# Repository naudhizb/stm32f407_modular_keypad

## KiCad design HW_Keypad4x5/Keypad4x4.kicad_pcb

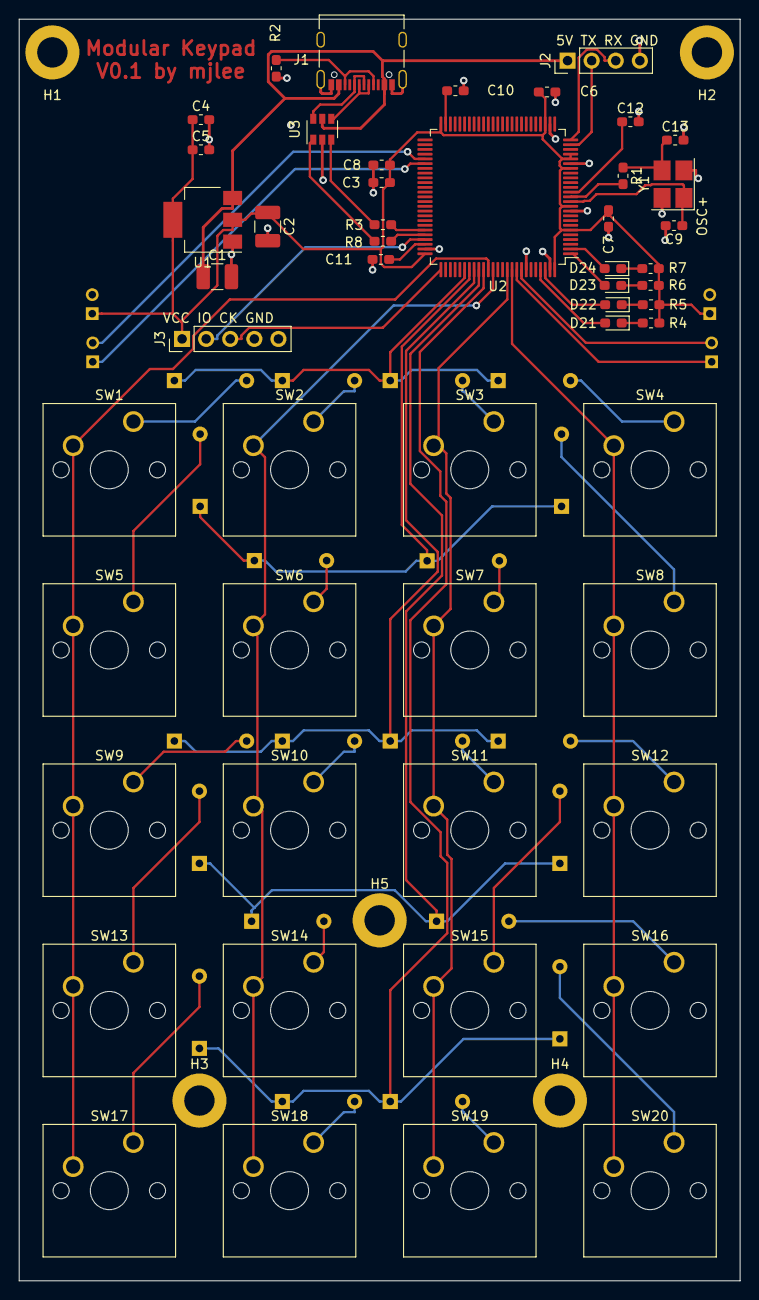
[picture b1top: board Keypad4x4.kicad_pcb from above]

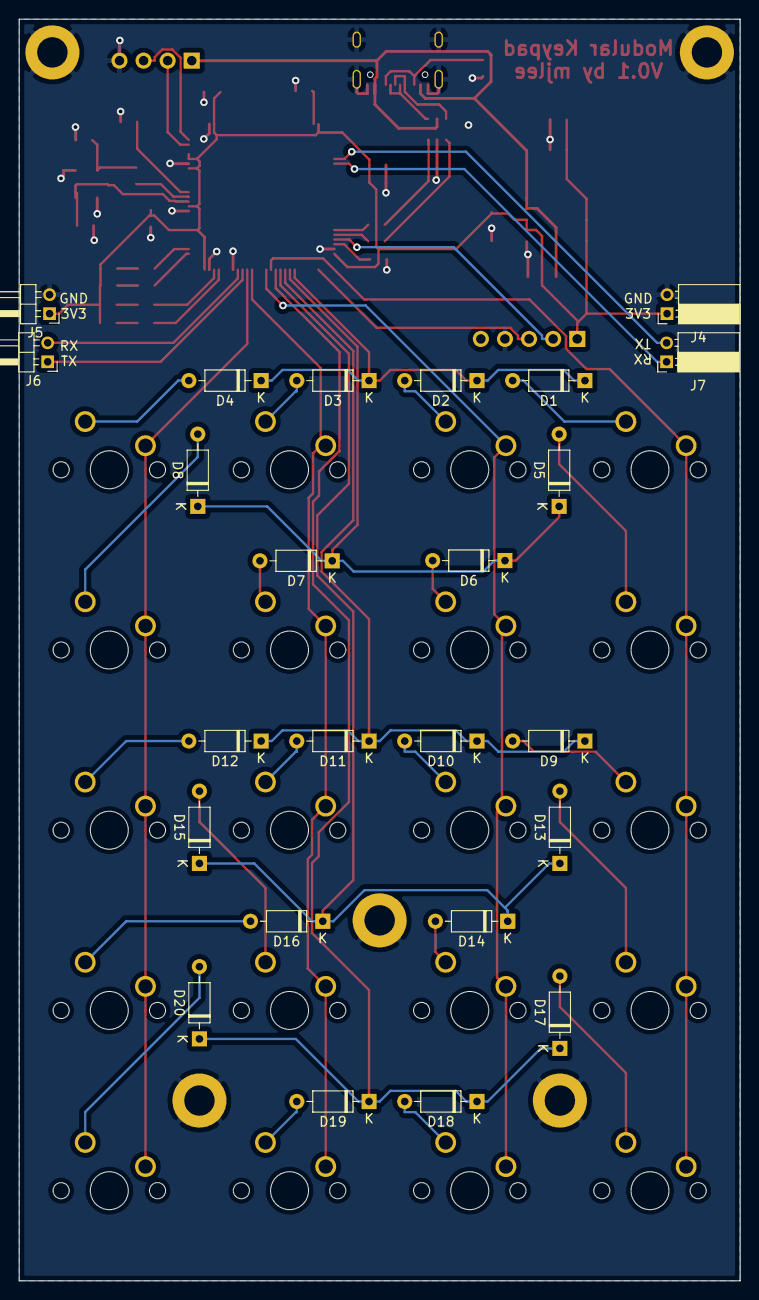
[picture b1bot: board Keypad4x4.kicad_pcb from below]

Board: 2 copper layers, 76.0 x 133.0 mm, 81 parts (24 on the bottom side), 61 nets.

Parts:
C1, C2: 10uF; C_1210_3225Metric_Pad1.42x2.65mm_HandSolder
C3: C475; C_0603_1608Metric_Pad1.05x0.95mm_HandSolder
C4, C5, C6, C7, C8, C12: C104; C_0603_1608Metric_Pad1.05x0.95mm_HandSolder
C9, C13: 12pF; C_0603_1608Metric_Pad1.05x0.95mm_HandSolder
C10, C11: C225; C_0603_1608Metric_Pad1.05x0.95mm_HandSolder
D1, D2, D3, D4, D5, D6, D7, D8, D9, D10, D11, D12, D13, D14, D15, D16, D17, D18, D19, D20: 1N4148; D_DO-35_SOD27_P7.62mm_Horizontal
D21, D22, D23, D24: LED; D_0603_1608Metric_Pad1.05x0.95mm_HandSolder
H1, H2, H3, H4, H5: MountingHole_3.2mm_M3_ISO7380_Pad
J1: USB_C_Receptacle_USB2.0; USB_C_Receptacle_Palconn_UTC16-G
J2: Conn_01x04; PinHeader_1x04_P2.54mm_Vertical
J3: Conn_01x05; PinHeader_1x05_P2.54mm_Vertical
J4: L_Power; PinSocket_1x02_P2.00mm_Horizontal
J5: R_Power; PinHeader_1x02_P2.00mm_Horizontal
J6: R_Comm; PinHeader_1x02_P2.00mm_Horizontal
J7: L_Comm; PinSocket_1x02_P2.00mm_Horizontal
R1: R470; C_0603_1608Metric_Pad1.05x0.95mm_HandSolder
R2: R513; C_0603_1608Metric_Pad1.05x0.95mm_HandSolder
R3, R8: R100; C_0603_1608Metric_Pad1.05x0.95mm_HandSolder
R4, R5, R6, R7: R471; C_0603_1608Metric_Pad1.05x0.95mm_HandSolder
SW1, SW2, SW3, SW4, SW5, SW6, SW7, SW8, SW9, SW10, SW11, SW12, SW13, SW14, SW15, SW16, SW17, SW18, SW19, SW20: SW_Push; SW_Cherry_MX_1.00u_PCB
U1: LM1117-3.3; SOT-223-3_TabPin2
U2: STM32F407VGTx; LQFP-100_14x14mm_P0.5mm
U3: USBLC6-2SC6; SOT-23-6
Y1: 25Mhz; Crystal_SMD_3225-4Pin_3.2x2.5mm_HandSoldering

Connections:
+3V3: C2.1, C3.1, C4.1, C5.1, C6.1, C7.1, C8.1, J3.1, J4.1, J5.1, R4.1, R5.1, R6.1, R7.1, U1.2, U2.6, U2.11, U2.19, U2.21, U2.22, U2.28, U2.50, U2.75, U2.100
+5VD: C1.1, J1.A4, J1.A9, J1.B4, J1.B9, J2.1, U1.3, U3.5
/Col0: SW1.2, SW5.2, SW9.2, SW13.2, SW17.2, U2.86
/Col1: SW2.2, SW6.2, SW10.2, SW14.2, SW18.2, U2.87
/Col2: SW3.2, SW7.2, SW11.2, SW15.2, SW19.2, U2.90
/Col3: SW4.2, SW8.2, SW12.2, SW16.2, SW20.2, U2.91
/DEBUG_RX: J2.3, U2.25
/DEBUG_TX: J2.2, U2.24
/LED0: D21.2, U2.97
/LED1: D22.2, U2.98
/LED2: D23.2, U2.1
/LED3: D24.2, U2.2
/L_RX: J7.1, U2.56
/L_TX: J7.2, U2.55
/NRST: C12.1, U2.14
/OSC+: C9.1, U2.12, Y1.1
/OSC-: R1.2, U2.13
/R_RX: J6.2, U2.93
/R_TX: J6.1, U2.92
/Row0: D1.1, D2.1, D3.1, D4.1, U2.81
/Row1: D5.1, D6.1, D7.1, D8.1, U2.82
/Row2: D9.1, D10.1, D11.1, D12.1, U2.83
/Row3: D13.1, D14.1, D15.1, D16.1, U2.84
/Row4: D17.1, D18.1, D19.1, D20.1, U2.85
/SWCLK: J3.3, U2.76
/SWDIO: J3.2, U2.72
/USBD+: R8.1, U2.71
/USBD-: R3.1, U2.70
/USBDM+: R8.2, U3.1
/USBDM-: R3.2, U3.3
/USB_CONN_N: J1.A7, J1.B7, U3.4
/USB_CONN_P: J1.A6, J1.B6, U3.6
/VCAP_1: C10.1, U2.49
/VCAP_2: C11.1, U2.73
GND: C1.2, C2.2, C3.2, C4.2, C5.2, C6.2, C7.2, C8.2, C9.2, C10.2, C11.2, C12.2, C13.2, H1.1, H2.1, H3.1, H4.1, H5.1, J1.A1, J1.A12, J1.B1, J1.B12, J1.S1, J2.4, J3.4, J4.2, J5.2, R2.1, U1.1, U2.10, U2.20, U2.27, U2.74, U2.94, U2.99, U3.2, Y1.2, Y1.4
unnamed: C13.1, R1.1, Y1.3
unnamed: D1.2, SW1.1
unnamed: D2.2, SW2.1
unnamed: D3.2, SW3.1
unnamed: D4.2, SW4.1
unnamed: D5.2, SW5.1
unnamed: D6.2, SW6.1
unnamed: D7.2, SW7.1
unnamed: D8.2, SW8.1
unnamed: D9.2, SW9.1
unnamed: D10.2, SW10.1
unnamed: D11.2, SW11.1
unnamed: D12.2, SW12.1
unnamed: D13.2, SW13.1
unnamed: D14.2, SW14.1
unnamed: D15.2, SW15.1
unnamed: D16.2, SW16.1
unnamed: D17.2, SW17.1
unnamed: D18.2, SW18.1
unnamed: D19.2, SW19.1
unnamed: D20.2, SW20.1
unnamed: D21.1, R4.2
unnamed: D22.1, R5.2
unnamed: D23.1, R6.2
unnamed: D24.1, R7.2
unnamed: J1.A5, J1.B5, R2.2

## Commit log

2021-03-10 Add Hardware
2021-03-20 Fix Error USBLC6-2SC6
